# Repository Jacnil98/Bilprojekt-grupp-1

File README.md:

# Bilprojekt-grupp-1
Bil projekt för ELA21 grupp 1

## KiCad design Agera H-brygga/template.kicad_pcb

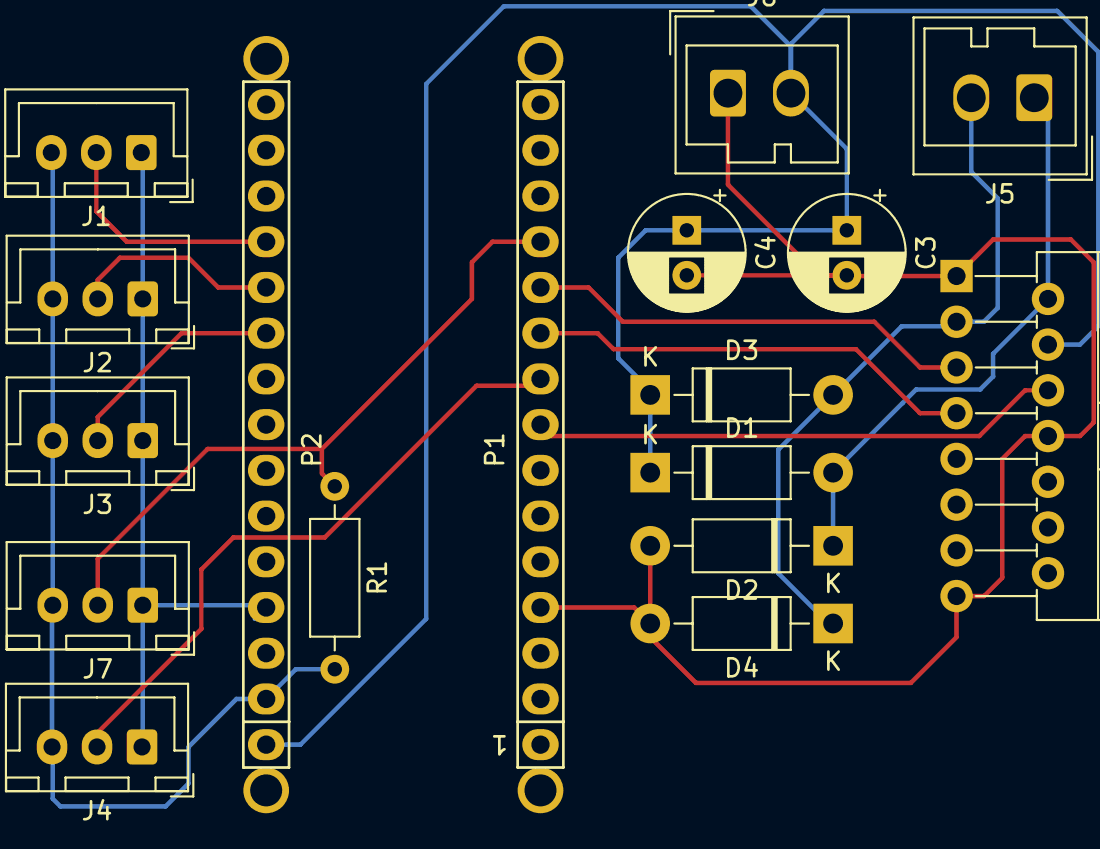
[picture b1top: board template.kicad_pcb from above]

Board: 2 copper layers, 21 parts (0 on the bottom side), 14 nets.

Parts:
C3: 100uf; CP_Radial_D6.3mm_P2.50mm
C4: 0.1uF; CP_Radial_D6.3mm_P2.50mm
D1, D2, D3, D4: 1N4007; D_DO-41_SOD81_P10.16mm_Horizontal
J1: sensor 1; JST_XH_B3B-XH-A_1x03_P2.50mm_Vertical
J2: sensor 2; JST_XH_B3B-XH-A_1x03_P2.50mm_Vertical
J3: sensor 3; JST_XH_B3B-XH-A_1x03_P2.50mm_Vertical
J4: SERVO; JST_XH_B3B-XH-A_1x03_P2.50mm_Vertical
J5: MOTOR; Wago_734-132_1x02_P3.50mm_Vertical
J6: POWER; Wago_734-132_1x02_P3.50mm_Vertical
J7: START; JST_XH_B3B-XH-A_1x03_P2.50mm_Vertical
P1: Digital; Socket_Strip_Arduino_1x15
P2: Analog; Socket_Strip_Arduino_1x15
P3, P4, P5, P6: CONN_01X01; 1pin_Nano
R1: R; R_Axial_DIN0207_L6.3mm_D2.5mm_P10.16mm_Horizontal
U1: L298HN; TO-220-15_P2.54x2.54mm_StaggerOdd_Lead4.58mm_Vertical

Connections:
5(**): P1.8, U1.6
6(**): J4.2, P1.9
7: P1.10, U1.7
8: P1.11, U1.5
9(**): J7.2, P1.12, R1.1
+5V: J1.1, J2.1, J3.1, J4.1, J7.1, P2.4
/Reset: P1.3, P2.3
A0: J1.2, P2.12
A1: J2.2, P2.11
A2: J3.2, P2.10
GND: C3.2, C4.2, D2.2, D4.2, J1.3, J2.3, J3.3, J4.3, J6.1, J7.3, P1.4, P2.2, R1.2, U1.1, U1.8, U1.15
unnamed: D1.2, D2.1, J5.1, U1.2
unnamed: D3.2, D4.1, J5.2, U1.3
Vin: C3.1, C4.1, D1.1, D3.1, J6.2, P2.1, U1.4

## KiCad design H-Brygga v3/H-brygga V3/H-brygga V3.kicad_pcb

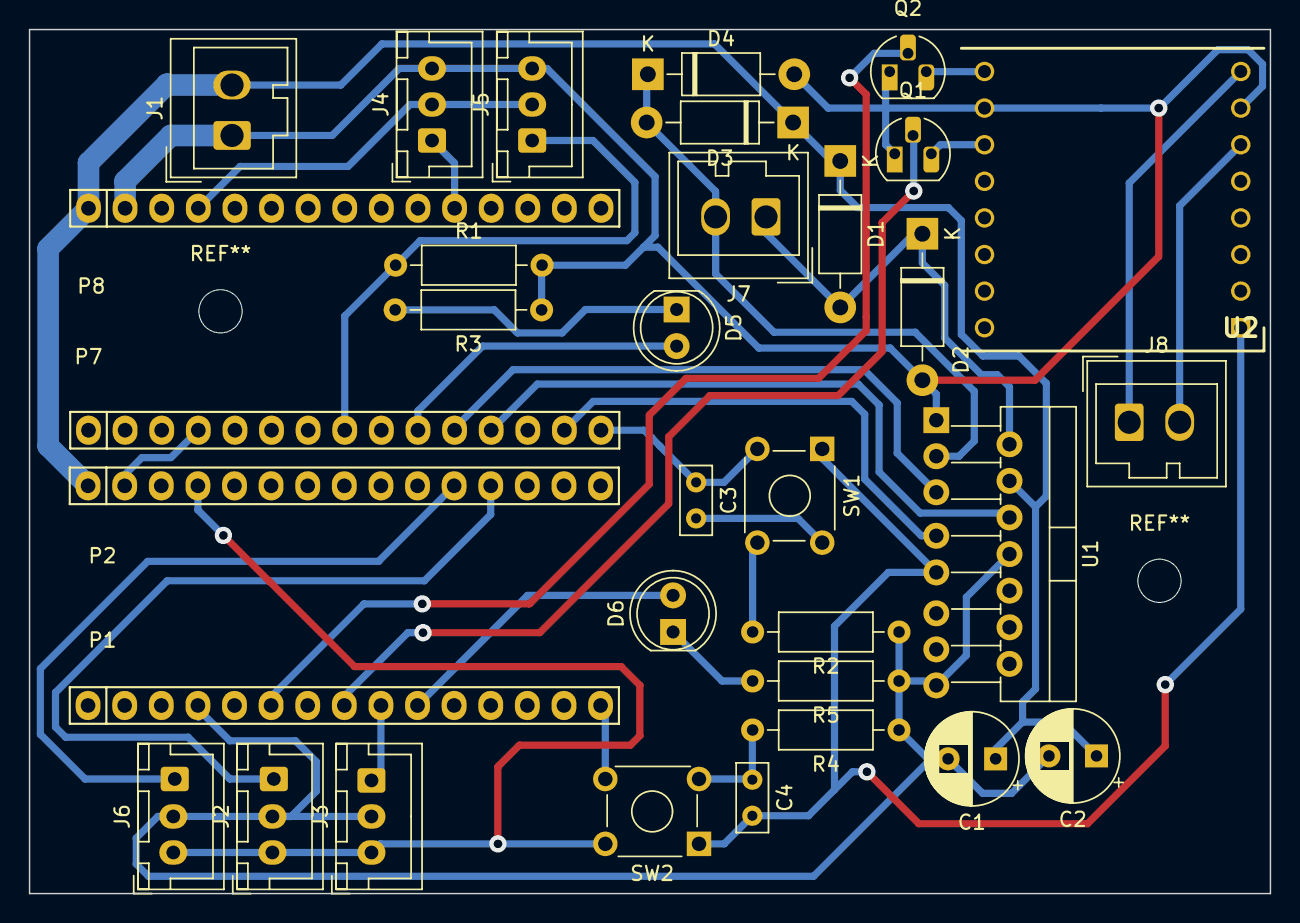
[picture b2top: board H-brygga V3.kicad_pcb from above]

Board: 2 copper layers, 86.1 x 60.0 mm, 33 parts (0 on the bottom side), 28 nets.

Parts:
C1: 100uf; CP_Radial_D6.3mm_P2.50mm
C2: 0.1uF; CP_Radial_D6.3mm_P2.50mm
C3, C4: C; C_Rect_L4.6mm_W2.0mm_P2.50mm_MKS02_FKP02
D1, D2, D3, D4: 1N4007; D_DO-41_SOD81_P10.16mm_Horizontal
D5, D6: LED; LED_D5.0mm
J1: POWER; Wago_734-132_1x02_P3.50mm_Vertical
J2: sensor vänster; JST_XH_B3B-XH-A_1x03_P2.50mm_Vertical
J3: SERVO; JST_XH_B3B-XH-A_1x03_P2.50mm_Vertical
J4: sensor motor; JST_XH_B3B-XH-A_1x03_P2.50mm_Vertical
J5: START; JST_XH_B3B-XH-A_1x03_P2.50mm_Vertical
J6: sensor höger; JST_XH_B3B-XH-A_1x03_P2.50mm_Vertical
J7: MOTOR; Wago_734-132_1x02_P3.50mm_Vertical
J8: Högtalare; Wago_734-132_1x02_P3.50mm_Vertical
P1, P7: Digital; Socket_Strip_Arduino_1x15
P2, P8: Analog; Socket_Strip_Arduino_1x15
Q1, Q2: Q_NMOS_DGS; TO-92_HandSolder
R1: R; R_Axial_DIN0207_L6.3mm_D2.5mm_P10.16mm_Horizontal
R2, R4: 10k; R_Axial_DIN0207_L6.3mm_D2.5mm_P10.16mm_Horizontal
R3, R5: 150; R_Axial_DIN0207_L6.3mm_D2.5mm_P10.16mm_Horizontal
SW1, SW2: SW_MEC_5E; SW_TH_Tactile_Omron_B3F-10xx
U1: L298HN; TO-220-15_P2.54x2.54mm_StaggerOdd_Lead4.58mm_Vertical
U2: DFR0299; DIPS1778W50P254L2100H170Q16N

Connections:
3(**).: P1.6, Q2.2 (G)
5(**): J5.1, P7.8, R1.1
5(**).: P1.8, Q1.2 (G)
6(**).: J3.1, P1.9
7.: D6.2 (A), P1.10
7a: D5.2 (A), P7.10
8a: P7.11, U1.5 (IN1)
9(**): P7.12, U1.6 (EnA)
11(**/MOSI): P7.14, U1.7 (IN2)
12(MISO): C3.1, P7.15, R2.2, SW1.3 (K), SW1.4 (A)
12(MISO).: C4.1, P1.15, R4.2, SW2.3 (K), SW2.4 (A)
+3V3: P2.14, P8.14
/Reset: P7.3, P8.3
/Reset.: P1.3, P2.3
A0.: J2.1, P2.12
A1: J4.1, P8.11
A1.: J6.1, P2.11
GND: C1.2, C2.2, D2.2 (A), D4.2 (A), J1.1, J2.3, J3.3, J4.3, J5.3, J6.3, P1.4, P2.2, P7.4, P8.2, Q1.1 (D), Q2.1 (D), R1.2, R2.1, R3.1, R4.1, R5.1, U1.1 (SENSE_A), U1.8 (GND), U1.15 (SENSE_B), U2.7 (GND_1), U2.10 (GND_2)
MP3+: C3.2, C4.2, J2.2, J3.2, J4.2, J5.2, J6.2, P2.4, P8.4, SW1.1, SW1.2, SW2.1, SW2.2, U1.9 (Vss), U2.1 (VCC)
unnamed: D1.2 (A), D2.1 (K), J7.1, U1.2 (OUT1)
unnamed: D3.2 (A), D4.1 (K), J7.2, U1.3 (OUT2)
unnamed: D5.1 (K), R3.2
unnamed: D6.1 (K), R5.2
unnamed: J8.1, U2.8 (SPK_2)
unnamed: J8.2, U2.6 (SPK_1)
unnamed: Q2.3 (S), U2.9 (IO_1)
unnamed: Q1.3 (S), U2.11 (IO_2)
Vin: C1.1, C2.1, D1.1 (K), D3.1 (K), J1.2, P2.1, P8.1, U1.4 (Vs)

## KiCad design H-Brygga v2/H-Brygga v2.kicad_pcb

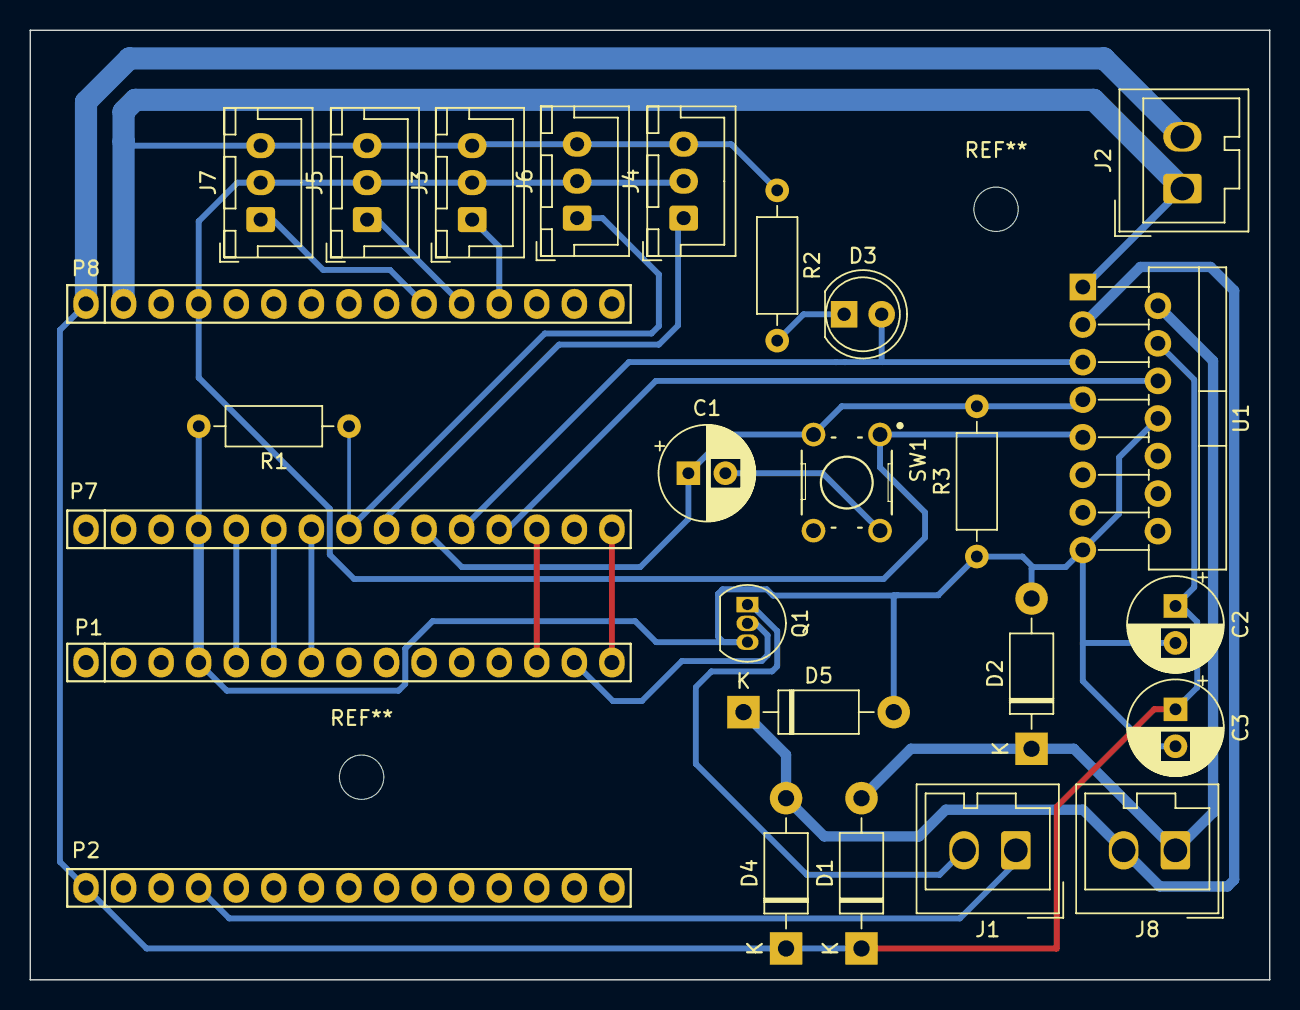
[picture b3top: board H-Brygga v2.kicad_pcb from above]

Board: 2 copper layers, 83.8 x 64.2 mm, 26 parts (0 on the bottom side), 25 nets.

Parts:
C1: C; CP_Radial_D6.3mm_P2.50mm
C2: 100uf; CP_Radial_D6.3mm_P2.50mm
C3: 0.1uF; CP_Radial_D6.3mm_P2.50mm
D1, D2, D4, D5: 1N4007; D_DO-41_SOD81_P10.16mm_Horizontal
D3: LED; LED_D5.0mm
J1: Högtalare; Wago_734-132_1x02_P3.50mm_Vertical
J2: POWER; Wago_734-132_1x02_P3.50mm_Vertical
J3: sensor 1; JST_XH_B3B-XH-A_1x03_P2.50mm_Vertical
J4: SERVO; JST_XH_B3B-XH-A_1x03_P2.50mm_Vertical
J5: sensor 2; JST_XH_B3B-XH-A_1x03_P2.50mm_Vertical
J6: START; JST_XH_B3B-XH-A_1x03_P2.50mm_Vertical
J7: sensor 3; JST_XH_B3B-XH-A_1x03_P2.50mm_Vertical
J8: MOTOR; Wago_734-132_1x02_P3.50mm_Vertical
P1, P7: Digital; Socket_Strip_Arduino_1x15
P2, P8: Analog; Socket_Strip_Arduino_1x15
Q1: BC547; TO-92_Inline
R1: R; R_Axial_DIN0207_L6.3mm_D2.5mm_P10.16mm_Horizontal
R2: 150; R_Axial_DIN0207_L6.3mm_D2.5mm_P10.16mm_Horizontal
R3: 10k; R_Axial_DIN0207_L6.3mm_D2.5mm_P10.16mm_Horizontal
SW1: SW_MEC_5E; SW_B3F-1000[1]
U1: L298HN; TO-220-15_P2.54x2.54mm_StaggerOdd_Lead4.58mm_Vertical

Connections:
2.: P1.5, P7.5
3(**): P1.6, P7.6
4.: P1.7, P7.7
5(**): J6.1, P7.8, R1.1
6(**): J4.1, P7.9
7a: C1.1, P7.10, R3.2, SW1.3 (K), U1.7 (IN2)
8a: D3.2 (A), P7.11, U1.5 (IN1)
9(**): P7.12, U1.6 (EnA)
10(**/SS).: P1.13, P7.13
11(**/MOSI).: P1.14, Q1.2 (B)
12(MISO).: P1.15, P7.15
+3V3: P2.14, P8.14
+5V: J1.1, J3.2, J4.2, J5.2, J6.2, J7.2, P2.4, P8.4, SW1.1, U1.9 (Vss)
/Reset: P7.3, P8.3
/Reset.: P1.3, P2.3
A0: J3.1, P8.12
A1: J5.1, P8.11
A2: J7.1, P8.10
GND: C2.2, C3.2, D2.2 (A), D5.2 (A), J2.1, J3.3, J4.3, J5.3, J6.3, J7.3, P1.4, P2.2, P7.4, P8.2, Q1.3 (E), R1.2, R2.1, R3.1, U1.1 (SENSE_A), U1.8 (GND), U1.15 (SENSE_B)
unnamed: C1.2, SW1.2
unnamed: D1.2 (A), D2.1 (K), J8.1, U1.2 (OUT1)
unnamed: D3.1 (K), R2.2
unnamed: D4.2 (A), D5.1 (K), J8.2, U1.3 (OUT2)
unnamed: J1.2, Q1.1 (C)
Vin: C2.1, C3.1, D1.1 (K), D4.1 (K), J2.2, P2.1, P8.1, U1.4 (Vs)

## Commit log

2022-02-24 Added Microchip files
2022-02-25 gjort viktig if sats
2022-02-25 Redigerade Daniels fel
2022-02-25 Tillägg av mappen för test koder
2022-02-25 Lade till filer för test av servo samt sensorer
2022-03-02 Kod för test av motor
2022-03-04 Kod för test av servo
2022-03-06 lagt till filer för NANO
2022-03-06 moddat för NANO git status help back
2022-03-06 kicad ritningar för arduino nano
2022-03-08 fixat servokoden
2022-03-08 Rensade
2022-03-08 Kod för test av GP2Y0A41SK0F
2022-03-09 Kod för sensor
2022-03-09 fixat servo PWM för NANO
2022-03-10 ändrade namn på daniels felstavningar
2022-03-22 Började med slutkoden
2022-03-24 början på feäääsh kod
2022-03-24 Ändrade i motorkod
2022-03-24 start på timer
2022-03-24 Jacob skrev koden för PWM-timer
2022-03-31 Kod för bil
2022-03-31 test
2022-03-31 Fixade daniels felstavningar :)
2022-03-31 tagit bort
2022-03-31 Strukturerade mappar
2022-04-01 motor pin tillagd
2022-04-01 fungerande kod med konstant 5v till motor
2022-04-01 timer0 för usart
2022-04-01 Började med kod för sensor
2022-04-02 börjat sätta ihop koden, timers på tur.
2022-04-02 fixat 4 fel
2022-04-02 felsökning
2022-04-02 det går åt skogen
2022-04-02 de ballar ur
2022-04-02 fixat fel med interrupts
2022-04-03 initierat Timer1 till pwm
2022-04-05 vidareutvecklat pwm
2022-04-05 testat sensorer, testar pwm
2022-04-05 vet inte
2022-04-06 fungerande pwm
2022-04-06 Jacob fixar allt!
2022-04-07 felsökt å fixat lite på pwm
2022-04-07 pwm togglar nu mellan on och off
2022-04-08 footprint för RP2040
2022-04-08 erik lagat pwm
2022-04-08 kommenterat och fixat pwm ihop med främre sensor
2022-04-11 lagt till servo class
2022-04-12 push for love
2022-04-12 push it to the limit
2022-04-12 för vem älskar inte git
2022-04-13 git var ännu roligare idag
2022-04-13 need i say moore
2022-04-13 Pushpress
2022-04-13 jacob e gris
2022-04-13 justerat koden
2022-04-13 fann ett fel
2022-04-13 smpfix
2022-04-14 KiCad fix
2022-04-14 fixat copy construct
2022-04-14 sparas
2022-04-14 funkar typ
2022-04-15 insignaler verkar ok, men inte regulate
2022-04-15 Ny h-brygga
2022-04-15 Rensat
2022-04-15 H-brygga
2022-04-15 för felsökning
2022-04-16 Brygga
2022-04-17 små ändringar
2022-04-17 lagt in eriks omgjorda variant i C++ och fått bort en bugg
2022-04-19 Uträkning för sensor
2022-04-19 främre sensorn implementerad för att styra hastighet
2022-04-19 mindre ändring
2022-04-20 start servo
2022-04-20 pushit
2022-04-20 fixat med servo
2022-04-21 typ klar med servo hoppas jag
2022-04-21 DONE
2022-04-23 H-brygga V3
2022-04-24 H-brygga inför fräsning
2022-04-27 Färdig H-brygga
2022-04-27 mjodå
2022-04-28 bra greje
2022-04-28 yes boss
2022-04-28 senaste
2022-05-03 Började med kod i C
2022-05-03 C-Kod servo
2022-05-03 header
2022-05-03 Kod för motor
2022-05-03 Filer för motor
2022-05-03 Fixat kod för motor
2022-05-03 Motor kod
2022-05-03 Kod bil motor
2022-05-04 Början kod för servo
2022-05-04 pwm igång
2022-05-05 motorn funkar
2022-05-09 kod servo
2022-05-09 Kod jacob motor
2022-05-10 funkar
2022-05-11 allt ok
2022-05-11 Kod bil jacob
2022-05-11 kod servo jacob
2022-05-15 byte
2022-05-15 yes med back
2022-05-16 Kod jacob
2022-05-17 last supper
2022-05-17 winner winner chicken dinner
2022-05-17 Orning och reda pengar på fredag
